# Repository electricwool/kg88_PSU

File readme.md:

## Garter Carriage PSU

- fits a garter carriage power supply box and the stock speed control knob
- speed control knob works in reverse due to limitations of simple switching power supplies and difficulty working with the 1k potentiometer. you can move one of the pot wires to the other side to fix this if it's important to you.
- takes a 15V supply
- provides a greater range of speed than normal
- 2A efuse functions to provides overcurrent/overtorque safety shutoff
- on my unit white wire is positive, black wire is negative
- tested with KG88 and KG89

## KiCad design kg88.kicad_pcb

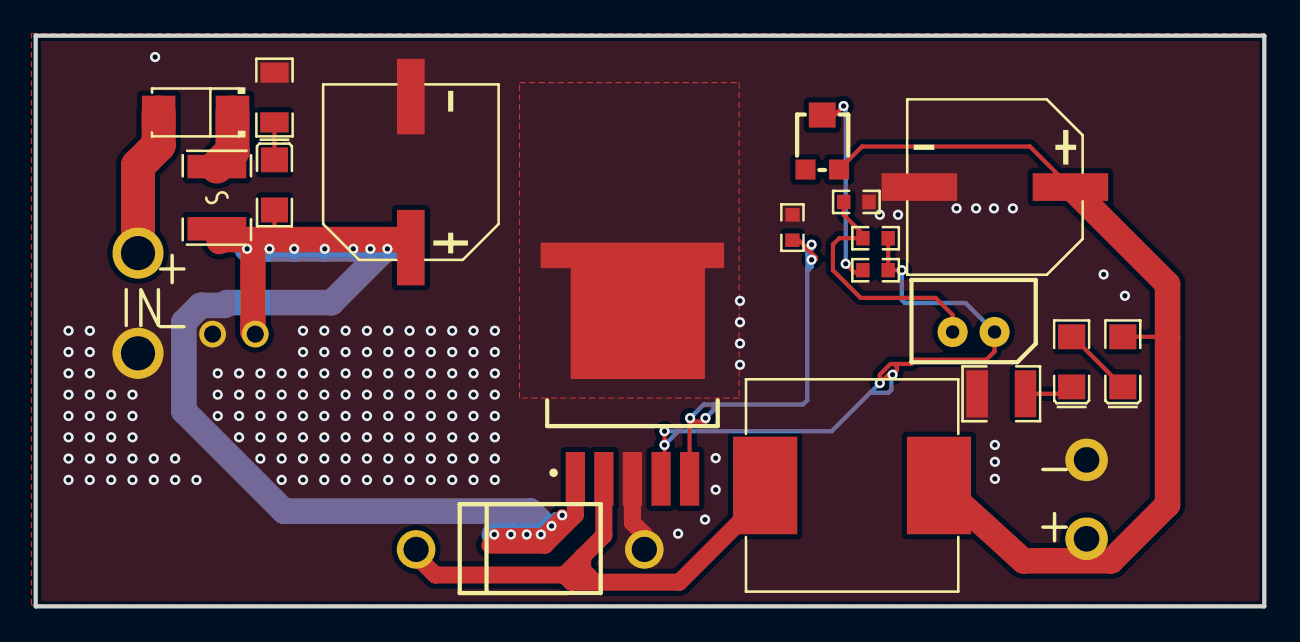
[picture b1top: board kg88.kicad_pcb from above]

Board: 2 copper layers, 73.2 x 34.0 mm, 18 parts (0 on the bottom side), 12 nets.

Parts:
1N5824: DO-27_BD5.3-L8.4-P12.40-D1.3-RD
68mH: IND-SMD_L12.5-W12.5
C1, C2: CAP-SMD_BD10.0-L10.3-W10.3-FD
CN1: CONN-TH_5267-02A
D1: SMA_L4.3-W2.6-LS5.2-RD
F1: F1812
LED1, LED2, LED3: LED1206-R-RD_GREEN
R1, R2, R3, R4: R0603
R5: R1206
R6: R1210
R7: RES-ADJ-SMD_JER33X-1-14
U2: TO-263-5_L10.2-W8.9-P1.70-TL

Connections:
$1N915: 1N5824.1, 68mH.1, U2.2
$1N1180: CN1.1, R2.2, R4.2, U2.4
$1N1219: CN1.2, R1.1, R4.1
$1N1297: R3.1, U2.5
$1N1694: LED1.2, R5.1
F1: D1.1, F1.2
GND: 1N5824.2, C1.2, C2.2, R1.2, R3.2, R5.2, R6.1, U2.3, U2.6
LED1: LED2.2, LED3.1
LED3: LED3.2, R6.2
TRIM: R2.1, R7.2
VIN: C2.1, F1.1, LED1.1, U2.1
VOUT: 68mH.2, C1.1, LED2.1, R7.1

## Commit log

2025-12-04 GarterCarriagePSU
2025-12-04 Refactor readme.md formatting and content
    Updated the formatting of the readme to use Markdown headers and improved clarity.
